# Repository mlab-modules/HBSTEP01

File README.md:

# HBSTEP01 - Stepper motor driver

The HBSTEP01 is a bipolar stepper motor driver module built around the STMicroelectronics L6470 chip. It provides a complete microstepping motor control solution with SPI interface, allowing for precise motor control and advanced motion features.

## Features

* Microstepping up to 1/128 steps
* Operating voltage: 8 V to 45 V
* Maximum output current: 3 A RMS (7 A peak)
* Integrated non-dissipative current sensing
* Programmable speed profiles and position control
* Sensorless stall detection
* Built-in motion engine with acceleration/deceleration control
* Two levels of overtemperature protection
* Overcurrent and undervoltage protection
* SPI interface (5 Mbps max)

## Typical Applications

* Precision motorized stages
* Robotics
* 3D printers
* Industrial automation

## Electrical Specifications

| Parameter                 | Value        |
| ------------------------- | ------------ |
| Supply Voltage (VS)       | 8 V to 45 V  |
| Logic Voltage (VDD)       | 3.3 V or 5 V |
| Max Output Current (RMS)  | 3 A          |
| Max Output Current (Peak) | 7 A          |
| SPI Clock Speed           | up to 5 MHz  |

## Connectors and Interfaces

* **Motor Outputs**: 4 terminals for bipolar stepper motor
* **Power Supply**: VIN and GND (external 8–45 V supply)
* **Logic Interface**: SPI (SDI, SDO, CS, CK), STBY, SW, BUSY/SYNC, FLAG

## Control Interface

The module is controlled via SPI. The L6470 accepts a variety of commands:

* Motion commands: `Run`, `Move`, `GoTo`, etc.
* Positioning: absolute and relative
* Speed and acceleration profile programming

Refer to the [L6470 datasheet](https://www.st.com/resource/en/datasheet/l6470.pdf) for detailed command structure and register settings.

## Protections

* Overcurrent detection with programmable threshold
* Thermal warning and shutdown
* Undervoltage lockout
* Open-drain FLAG pin indicates fault conditions

## PCB Dimensions and Mounting

* Standard MLAB format
* Mounting holes compatible with other MLAB modules

## Resources

* [L6470 Datasheet (ST)](https://www.st.com/resource/en/datasheet/l6470.pdf)
* MLAB Wiki: [HBSTEP01](https://wiki.mlab.cz/doku.php?id=en:hbstep01)

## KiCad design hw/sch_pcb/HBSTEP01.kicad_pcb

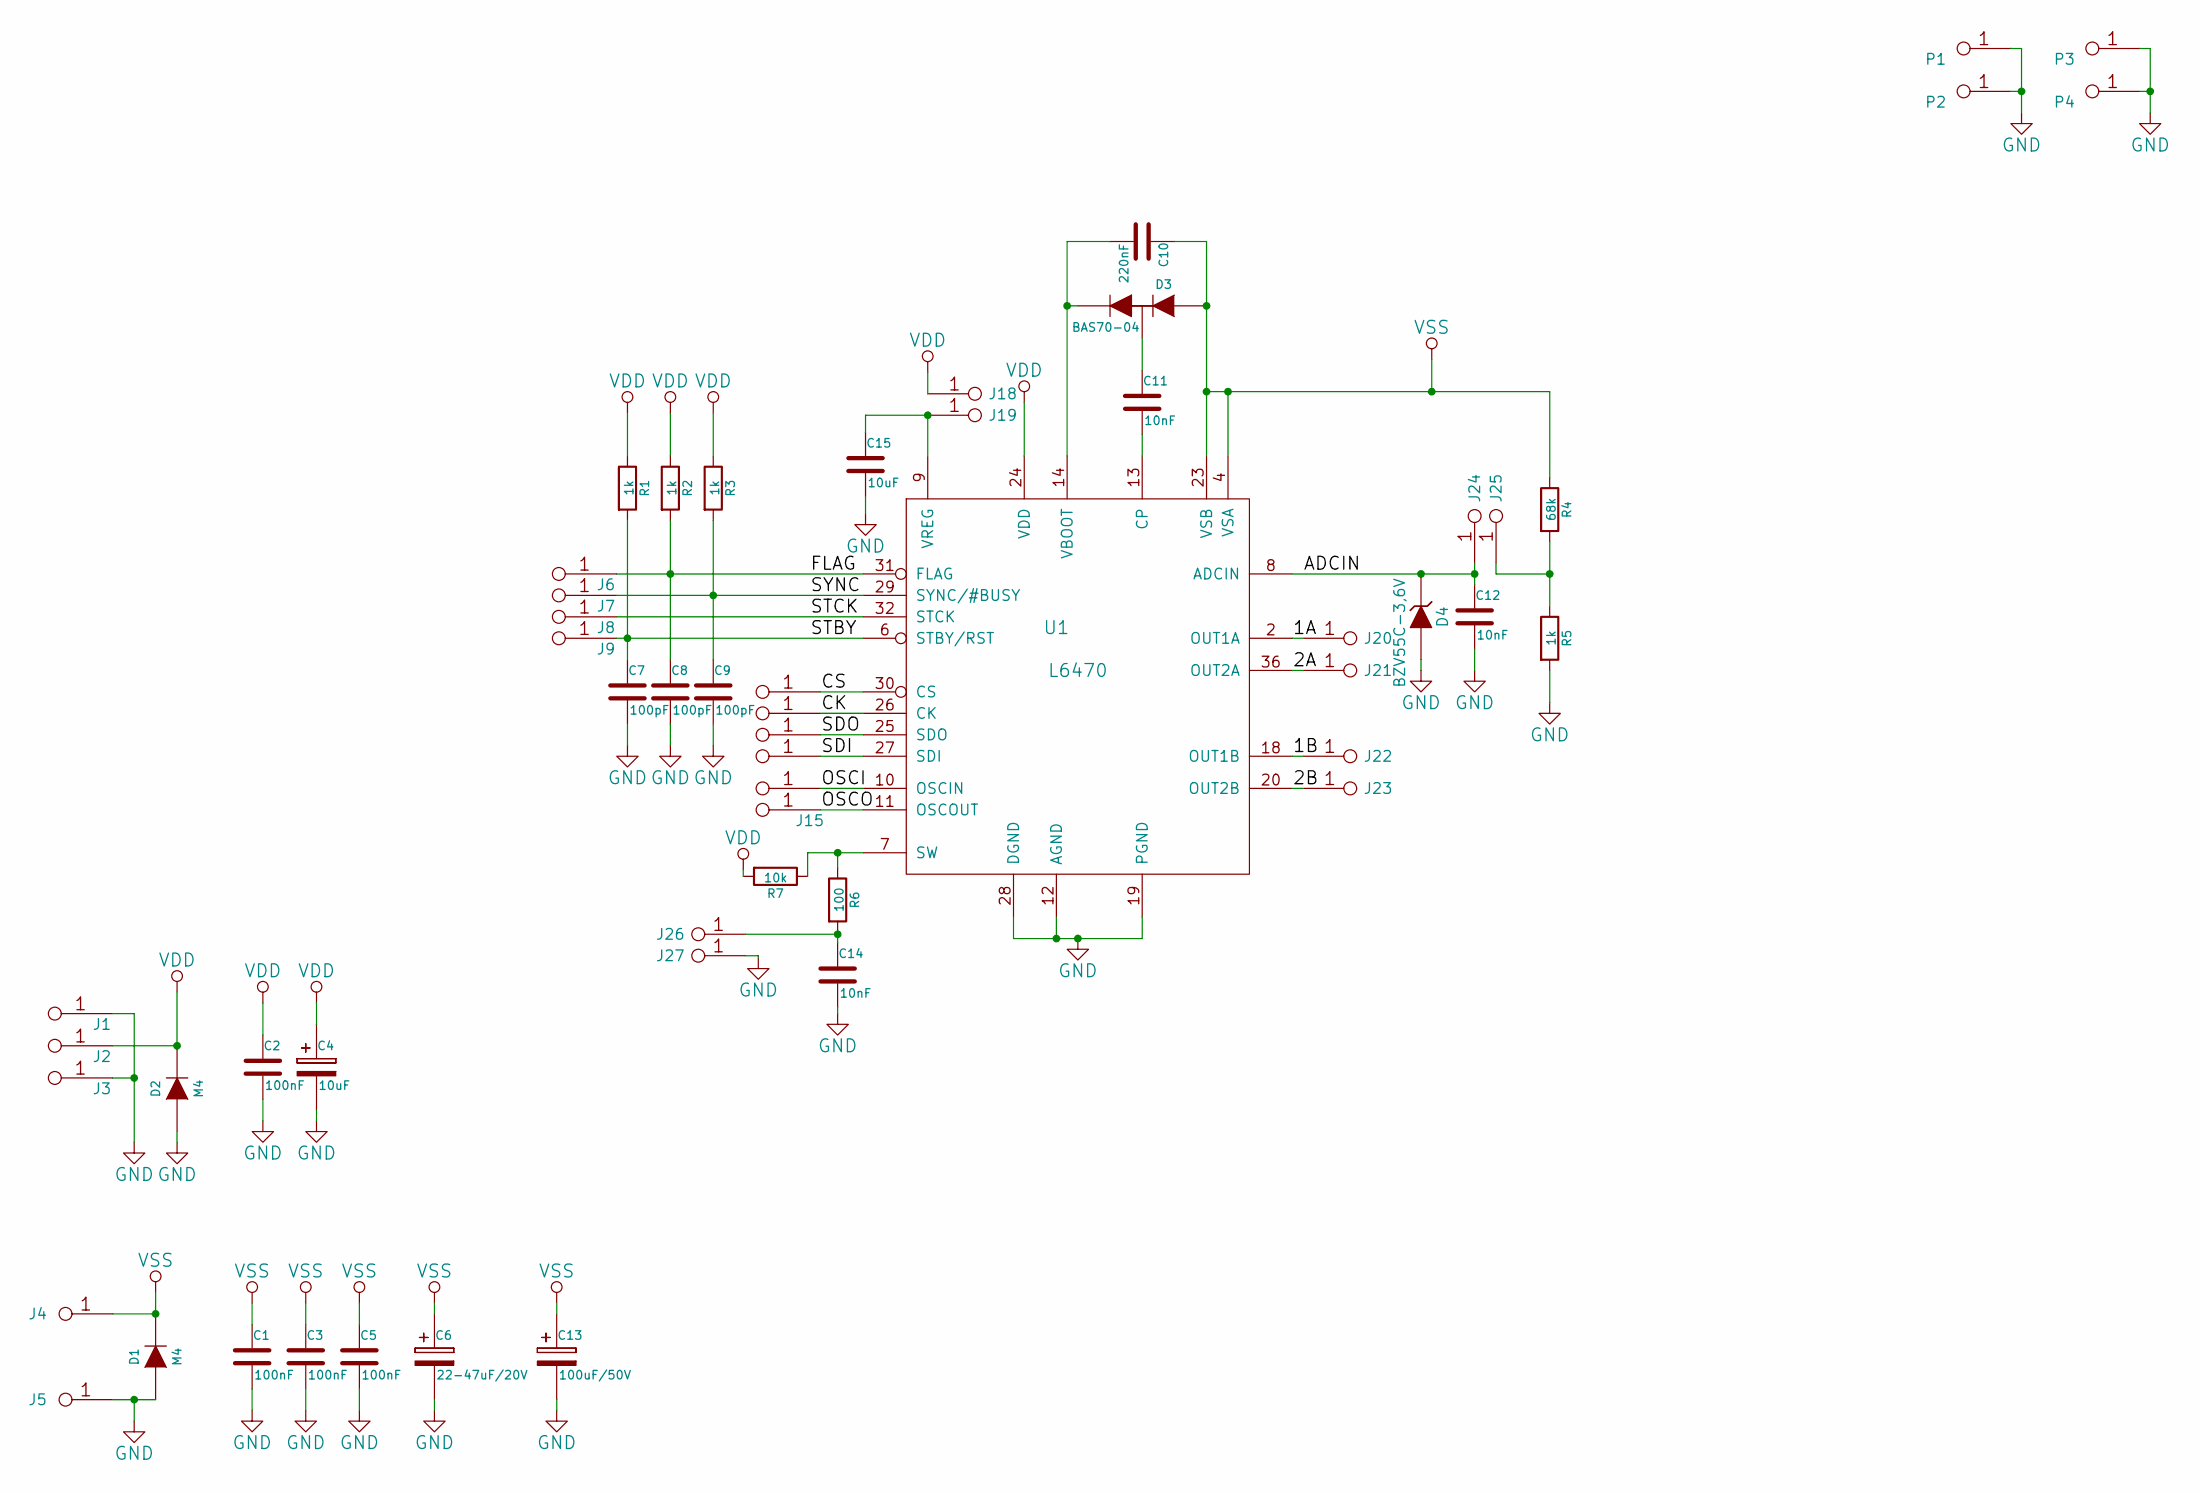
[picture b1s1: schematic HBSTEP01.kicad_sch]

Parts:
C1, C2, C3, C5: 100nF; SMD-0805
C4: 10uF; TantalC_SizeB_Reflow
C6: 22-47uF/20V; TantalC_SizeC_Reflow
C7, C8, C9: 100pF; SMD-0805
C10: 220nF; SMD-0805
C11, C12, C14: 10nF; SMD-0805
C13: 100uF/50V; Elko_vert_11x5mm_RM2_CopperClear
C15: 10uF; SMD-0805
D1, D2: M4; SMA_Standard
D3: BAS70-04; SOT-23
D4: BZV55C-3,6V
J1, J2, J3, J6, J7, J8, J9, J10, J11, J12, J13, J14, J15: JUMP_2x1; Straight_2x01
J4, J5: CONN1_1; WAGO256
J18, J19, J24, J25, J26, J27: CONN1_1; Straight_1x01
J20, J21, J22, J23: CONN1_1; WAGO256_2
P1, P2, P3, P4: sroub; MountingHole_3mm
R1, R2, R3, R5: 1k; SMD-0805
R4: 68k; SMD-0805
R6: 100; SMD-0805
R7: 10k; SMD-0805
U1: L6470; POWERSO36

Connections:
/1A: J20.1, U1.2 (OUT1A), U1.3 (OUT1A)
/1B: J22.1, U1.17 (OUT1B), U1.18 (OUT1B)
/2A: J21.1, U1.35 (OUT2A), U1.36 (OUT2A)
/2B: J23.1, U1.20 (OUT2B), U1.21 (OUT2B)
/ADCIN: C12.1, D4.2 (K), J24.1, U1.8 (ADCIN)
/CK: J11.1, J11.2, U1.26 (CK)
/CS: J10.1, J10.2, U1.30 (CS)
/FLAG: C8.1, J6.1, J6.2, R2.2, U1.31 (FLAG)
/OSCI: J14.1, J14.2, U1.10 (OSCIN)
/OSCO: J15.1, J15.2, U1.11 (OSCOUT)
/SDI: J13.1, J13.2, U1.27 (SDI)
/SDO: J12.1, J12.2, U1.25 (SDO)
/STBY: C7.1, J9.1, J9.2, R1.2, U1.6 (STBY/RST)
/STCK: J8.1, J8.2, U1.32 (STCK)
/SYNC: C9.1, J7.1, J7.2, R3.2, U1.29 (SYNC/#BUSY)
GND: C1.2, C2.2, C3.2, C4.2, C5.2, C6.2, C7.2, C8.2, C9.2, C12.2, C13.2, C14.2, C15.2, D1.1 (A), D2.1 (A), D4.1 (A), J1.1, J1.2, J3.1, J3.2, J5.1, J27.1, P1.1, P2.1, P3.1, P4.1, R5.2, U1.1 (PGND), U1.12 (AGND), U1.19 (PGND), U1.28 (DGND), U1.50 (PGND), U1.51 (PGND), U1.52 (PGND)
unnamed: C10.2, D3.2 (A), U1.14 (VBOOT)
unnamed: C11.1, D3.3 (m)
unnamed: C11.2, U1.13 (CP)
unnamed: C14.1, J26.1, R6.2
unnamed: C15.1, J19.1, U1.9 (VREG)
unnamed: J25.1, R4.2, R5.1
unnamed: R6.1, R7.1, U1.7 (SW)
VDD: C2.1, C4.1, D2.2 (K), J2.1, J2.2, J18.1, R1.1, R2.1, R3.1, R7.2, U1.24 (VDD)
VSS: C1.1, C3.1, C5.1, C6.1, C10.1, C13.1, D1.2 (K), D3.1 (A), J4.1, R4.1, U1.4 (VSA), U1.5 (VSA), U1.15 (VSB), U1.16 (VSB), U1.22 (VSB), U1.23 (VSB), U1.33 (VSA), U1.34 (VSA)

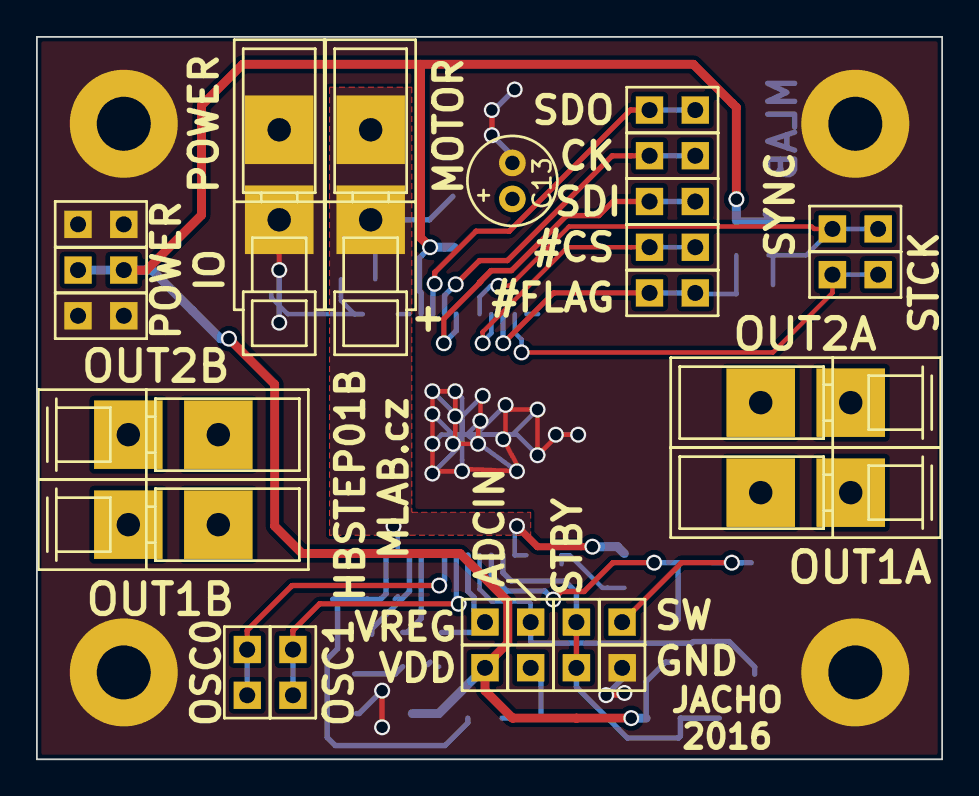
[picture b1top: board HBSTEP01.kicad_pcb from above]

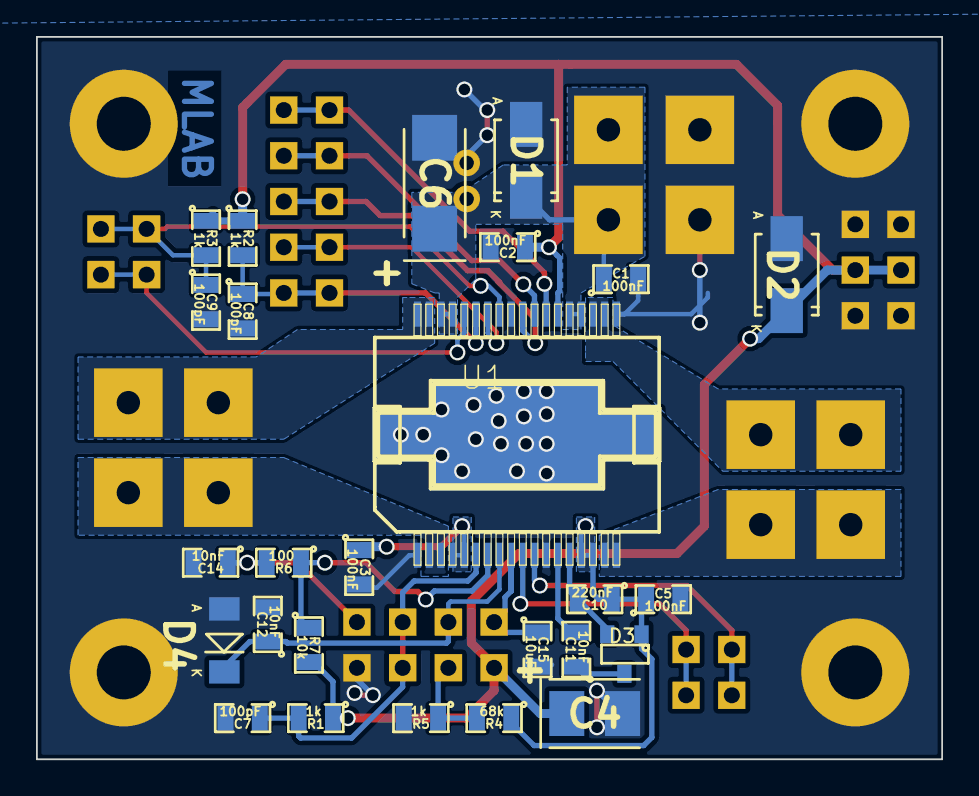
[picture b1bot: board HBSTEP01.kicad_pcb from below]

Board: 2 copper layers, 50.3 x 40.1 mm, 56 parts (26 on the bottom side), 25 nets.

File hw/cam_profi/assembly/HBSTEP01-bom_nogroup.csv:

Component,Description,Part,References,Value,Footprint,Quantity Per PCB,Datasheet
1,,C_13,C7,100pF,SMD-0805,1,
2,,C_14,C8,100pF,SMD-0805,1,
3,,C_15,C9,100pF,SMD-0805,1,
4,,C_17,C11,10nF,SMD-0805,1,
5,,C_23,C12,10nF,SMD-0805,1,
6,,C_18,C14,10nF,SMD-0805,1,
7,,C_21,C1,100nF,SMD-0805,1,
8,,C_24,C2,100nF,SMD-0805,1,
9,,C_19,C3,100nF,SMD-0805,1,
10,,C_20,C5,100nF,SMD-0805,1,
11,,C_16,C10,220nF,SMD-0805,1,
12,,C_22,C15,10uF,SMD-0805,1,
13,,CP2_6,C4,10uF,TantalC_SizeB_Reflow,1,
14,,CP2_5,C13,100uF/50V,Elko_vert_11x5mm_RM2_CopperClear,1,
15,,CP2_4,C6,22-47uF/20V,TantalC_SizeC_Reflow,1,
16,,BAT46SW_2,D3,BAS70-04,SOT-23,1,
17,,D_ZENER_2,D4,"BZV55C-3,6V",,1,
18,,DIODE_3,D1,M4,SMA_Standard,1,
19,,DIODE_4,D2,M4,SMA_Standard,1,
20,,CONN1_1_22,J18,CONN1_1,Straight_1x01,1,
21,,CONN1_1_21,J19,CONN1_1,Straight_1x01,1,
22,,CONN1_1_17,J20,CONN1_1,WAGO256_2,1,
23,,CONN1_1_18,J21,CONN1_1,WAGO256_2,1,
24,,CONN1_1_19,J22,CONN1_1,WAGO256_2,1,
25,,CONN1_1_20,J23,CONN1_1,WAGO256_2,1,
26,,CONN1_1_15,J24,CONN1_1,Straight_1x01,1,
27,,CONN1_1_16,J25,CONN1_1,Straight_1x01,1,
28,,CONN1_1_13,J26,CONN1_1,Straight_1x01,1,
29,,CONN1_1_14,J27,CONN1_1,Straight_1x01,1,
30,,CONN1_1_23,J4,CONN1_1,WAGO256,1,
31,,CONN1_1_24,J5,CONN1_1,WAGO256,1,
32,,JUMP_2x1_24,J1,JUMP_2x1,Straight_2x01,1,
33,,JUMP_2x1_22,J10,JUMP_2x1,Straight_2x01,1,
34,,JUMP_2x1_23,J11,JUMP_2x1,Straight_2x01,1,
35,,JUMP_2x1_21,J12,JUMP_2x1,Straight_2x01,1,
36,,JUMP_2x1_14,J13,JUMP_2x1,Straight_2x01,1,
37,,JUMP_2x1_15,J14,JUMP_2x1,Straight_2x01,1,
38,,JUMP_2x1_16,J15,JUMP_2x1,Straight_2x01,1,
39,,JUMP_2x1_25,J2,JUMP_2x1,Straight_2x01,1,
40,,JUMP_2x1_26,J3,JUMP_2x1,Straight_2x01,1,
41,,JUMP_2x1_20,J6,JUMP_2x1,Straight_2x01,1,
42,,JUMP_2x1_19,J7,JUMP_2x1,Straight_2x01,1,
43,,JUMP_2x1_18,J8,JUMP_2x1,Straight_2x01,1,
44,,JUMP_2x1_17,J9,JUMP_2x1,Straight_2x01,1,
45,,R_9,R6,100,SMD-0805,1,
46,,R_12,R1,1k,SMD-0805,1,
47,,R_11,R2,1k,SMD-0805,1,
48,,R_10,R3,1k,SMD-0805,1,
49,,R_14,R5,1k,SMD-0805,1,
50,,R_8,R7,10k,SMD-0805,1,
51,,R_13,R4,68k,SMD-0805,1,
52,,L6470_2,U1,L6470,POWERSO36,1,

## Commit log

2023-04-01 Adding force option to enable splitting in not fresh copy of Modules repository.
2023-09-17 automated commit; add github actions
2023-09-17 Update workflow files
2023-09-17 Update metadata files
2025-08-19 Update project to KiCAD9.
2025-08-19 Cleanup KiCAD project.
2025-08-19 Update actions products
2025-08-19 Update readme.
2025-08-19 Change title image.
